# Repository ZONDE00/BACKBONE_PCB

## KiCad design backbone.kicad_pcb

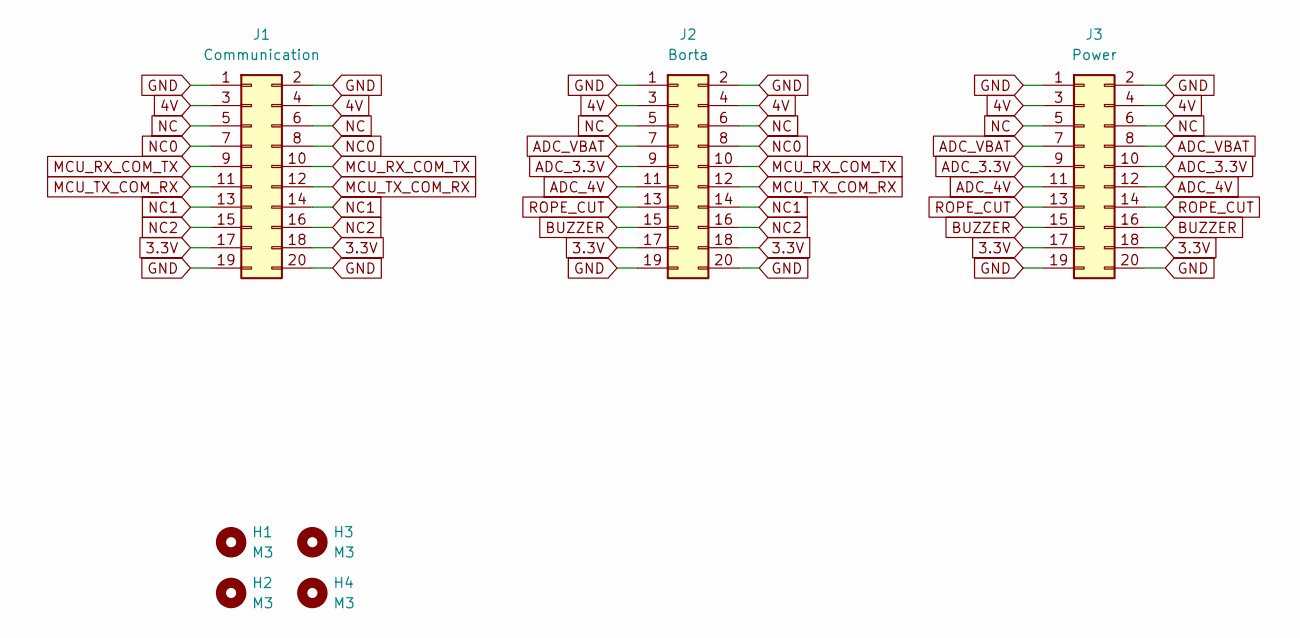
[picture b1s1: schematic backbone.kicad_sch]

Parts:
H1, H2, H3, H4: M3; MountingHole_3.2mm_M3
J1: Communication; PinSocket_2x10_P2.54mm_Vertical
J2: Borta; PinSocket_2x10_P2.54mm_Vertical
J3: Power; PinSocket_2x10_P2.54mm_Vertical

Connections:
3.3V: J1.17, J1.18, J2.17, J2.18, J3.17, J3.18
4V: J1.3, J1.4, J2.3, J2.4, J3.3, J3.4
ADC_3.3V: J2.9, J3.9, J3.10
ADC_4V: J2.11, J3.11, J3.12
ADC_VBAT: J2.7, J3.7, J3.8
BUZZER: J2.15, J3.15, J3.16
GND: J1.1, J1.2, J1.19, J1.20, J2.1, J2.2, J2.19, J2.20, J3.1, J3.2, J3.19, J3.20
MCU_RX_COM_TX: J1.9, J1.10, J2.10
MCU_TX_COM_RX: J1.11, J1.12, J2.12
NC: J1.5, J1.6, J2.5, J2.6, J3.5, J3.6
NC0: J1.7, J1.8, J2.8
NC1: J1.13, J1.14, J2.14
NC2: J1.15, J1.16, J2.16
ROPE_CUT: J2.13, J3.13, J3.14

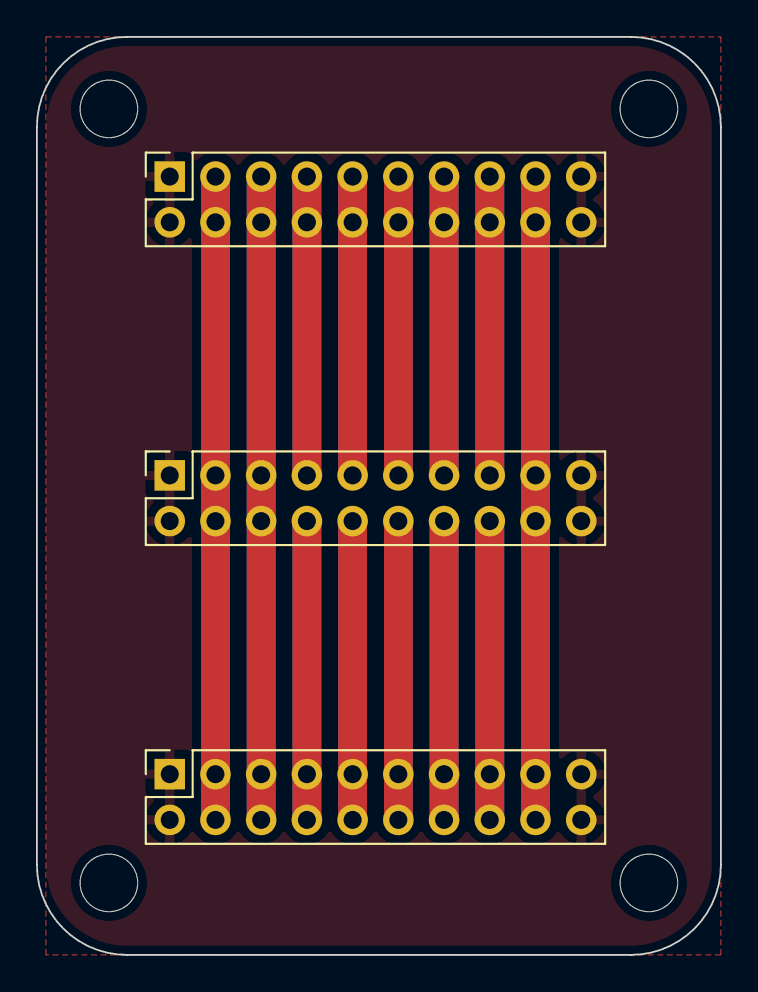
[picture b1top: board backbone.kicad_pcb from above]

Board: 2 copper layers, 38.0 x 51.0 mm, 7 parts (0 on the bottom side), 14 nets.

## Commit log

2022-07-30 IRBE_5 BACKBONE
    IRBE-5 mugurkaula KiCad projekts 1.0 versija.
2022-09-25 0.1v
    Ridiculess backbone
